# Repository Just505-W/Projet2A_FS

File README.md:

# Projet2A\_FS

Bienvenu sur le dépot GitHub d'un des groupes de Projet de deuxième année de l'ENSEA.  
Participants du projet :  
WOELFFEL Justine           NOICI Amélie  
IGIER Charles                  FORBICE Mattéo  
GERVAIS Joseph

Professeur encadrant : M.Seigneurbieux

Ce projet a pour objectif de réaliser des composants utiles au bon fonctionnement d'une monoplace dans le cadre du concours **FORMULA STUDENT**. Nous avions déjà réalisé plusieurs cartes l'année passée - il s'agit d'un odomètre, BMS, datalogger, carte de puissance et carte de contrôle. Nous allons reprendre ces carte avec pour objectif que concevoir une première version de ce que l'on voudra à terme présenter au concours.

## Objectifs

|MÉCANIQUE|ÉLECTRIQUE DE PUISSANCE|ÉLECTRONIQUE BASSE TENSION|LOGICIEL|SÉCURITÉ|GESTION DE PROJET|
|:-:|:-:|:-:|:-:|:-:|:-:|
|Châssis|Batterie|Alimentation 12 V|Firmware|Arrêt d'urgence|Planning|
|Suspension|BMS|Microcontrôleur|Contrôle moteur|Isolation|Budget|
|Direction|Contacteurs|Capteurs|Acquisition|Coupure HV|Achats|
|Freinage|Précharge|Acquisition|Télémétrie|Interlocks|Fabrication|
|Roues/pneus|Fusibles|Température|Diagnostic|Protection contre les défauts|Documentation|
|Transmission|Distribution HV|Instrumentation|Interface éventuelle|Sécurité batterie|Tests|
|Supports moteur|Moteur|Courant|Gestion des erreurs|Sécurité mécanique|Validation|
|Ergonomie|Onduleur|Tension||Procédures de test|Règlement|
|Carrosserie éventuelle|Câblage|Vitesse||||
||Protections|Communication CAN||||
||Isolation|||||

:warning:

### Important : Soutenance le 15 décembre

#### Checklist : 

* Définir le rôle de chacun : 

  * Définir les tâches que chacun doit accomplir
* Faire le Gantt (ou du moins ce qu'il faut faire et quand il faut le faire)
* Documentation de ce qui à été fait :

  * Regrouper toutes les documentations
  * Objectifs ?
  * Conclusion lors du 15 décembre
  * Ce qu'on espère avant la prochaine soutenance

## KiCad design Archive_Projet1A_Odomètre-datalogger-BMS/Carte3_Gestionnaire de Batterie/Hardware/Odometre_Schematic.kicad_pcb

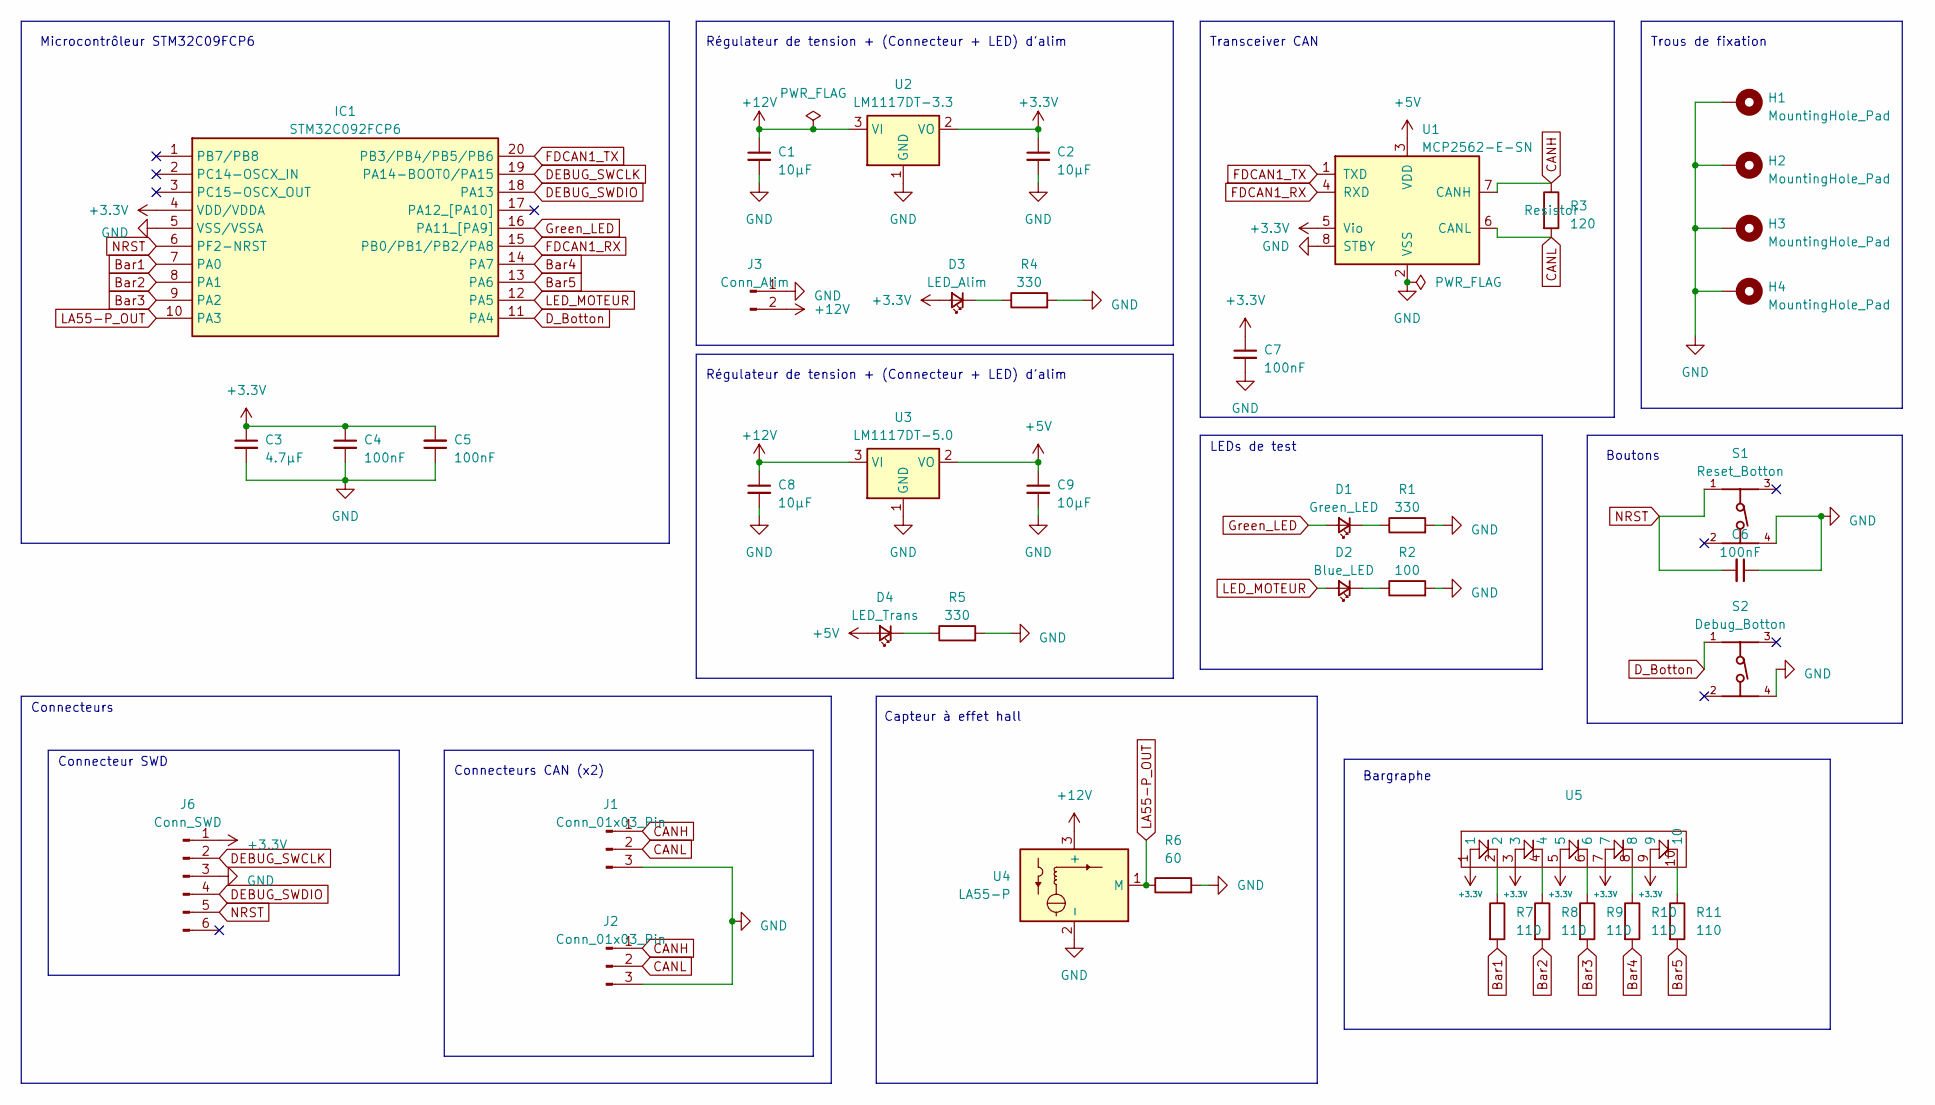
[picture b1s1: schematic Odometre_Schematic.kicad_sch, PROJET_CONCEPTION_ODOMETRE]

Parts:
C1, C2, C8, C9: 10µF; C_0805_2012Metric_Pad1.18x1.45mm_HandSolder
C3: 4.7µF; C_0805_2012Metric_Pad1.18x1.45mm_HandSolder
C4, C5, C6, C7: 100nF; C_0805_2012Metric_Pad1.18x1.45mm_HandSolder
D1: Green_LED; D_0603_1608Metric_Pad1.05x0.95mm_HandSolder
D2: Blue_LED; D_0603_1608Metric_Pad1.05x0.95mm_HandSolder
D3: LED_Alim; D_0603_1608Metric_Pad1.05x0.95mm_HandSolder
D4: LED_Trans; D_0603_1608Metric_Pad1.05x0.95mm_HandSolder
H1, H2, H3, H4: MountingHole_Pad; MountingHole_3.2mm_M3_DIN965_Pad
IC1: STM32C092FCP6; SOP65P640X120-20N; Manufacturer_Part_Number STM32C092FCP6
J1, J2: Conn_01x03_Pin; JST_PH_B3B-PH-K_1x03_P2.00mm_Vertical
J3: Conn_Alim; JST_PH_B2B-PH-K_1x02_P2.00mm_Vertical
J6: Conn_SWD; PinHeader_1x06_P2.54mm_Vertical
R1, R4, R5: 330; R_0603_1608Metric_Pad0.98x0.95mm_HandSolder
R2: 100; R_0603_1608Metric_Pad0.98x0.95mm_HandSolder
R3: 120; R_0603_1608Metric_Pad0.98x0.95mm_HandSolder
R6: 60; R_0603_1608Metric_Pad0.98x0.95mm_HandSolder
R7, R8, R9, R10, R11: 110; R_0603_1608Metric_Pad0.98x0.95mm_HandSolder
S1: Reset_Botton; 430182043816
S2: Debug_Botton; 430182043816
U1: MCP2562-E-SN; SOIC-8_3.9x4.9mm_P1.27mm
U2: LM1117DT-3.3; TO-252-3_TabPin2
U3: LM1117DT-5.0; TO-252-3_TabPin2
U4: LA55-P
U5: Projo

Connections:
+3.3V: C2.1, C3.1, C4.1, C5.2, C7.1, D3.2 (A), IC1.4 (VDD/VDDA), J6.1, U1.5 (Vio), U2.2 (VO), U5.1, U5.3, U5.5, U5.7, U5.9
+5V: C9.1, D4.2 (A), U1.3 (VDD), U3.2 (VO)
+12V: C1.1, C8.1, J3.2, U2.3 (VI), U3.3 (VI), U4.3 (+)
Bar1: IC1.7 (PA0), R7.2
Bar2: IC1.8 (PA1), R8.2
Bar3: IC1.9 (PA2), R9.2
Bar4: IC1.14 (PA7), R10.2
Bar5: IC1.13 (PA6), R11.2
CANH: J1.1, J2.1, R3.1, U1.7 (CANH)
CANL: J1.2, J2.2, R3.2, U1.6 (CANL)
DEBUG_SWCLK: IC1.19 (PA14-BOOT0/PA15), J6.2
DEBUG_SWDIO: IC1.18 (PA13), J6.4
D_Botton: IC1.11 (PA4), S2.1
FDCAN1_RX: IC1.15 (PB0/PB1/PB2/PA8), U1.4 (RXD)
FDCAN1_TX: IC1.20 (PB3/PB4/PB5/PB6), U1.1 (TXD)
GND: C1.2, C2.2, C3.2, C4.2, C5.1, C6.1, C7.2, C8.2, C9.2, H1.1, H2.1, H3.1, H4.1, IC1.5 (VSS/VSSA), J1.3, J2.3, J3.1, J6.3, R1.2, R2.2, R4.2, R5.2, R6.2, S1.4, S2.4, U1.2 (VSS), U1.8 (STBY), U2.1 (GND), U3.1 (GND), U4.2 (-)
Green_LED: D1.2 (A), IC1.16 (PA11_[PA9])
LA55-P_OUT: IC1.10 (PA3), R6.1, U4.1 (M)
LED_MOTEUR: D2.2 (A), IC1.12 (PA5)
NRST: C6.2, IC1.6 (PF2-NRST), J6.5, S1.1
unnamed: D1.1 (K), R1.1
unnamed: D2.1 (K), R2.1
unnamed: D3.1 (K), R4.1
unnamed: D4.1 (K), R5.1
unnamed: R7.1, U5.2
unnamed: R8.1, U5.4
unnamed: R9.1, U5.6
unnamed: R10.1, U5.8
unnamed: R11.1, U5.10

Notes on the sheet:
LEDs de test
Transceiver CAN
Connecteurs CAN (x2)
Régulateur de tension + (Connecteur + LED) d'alim
Connecteur SWD
Capteur à effet hall
Connecteurs
Boutons
Bargraphe
Microcontrôleur STM32C09FCP6
Trous de fixation

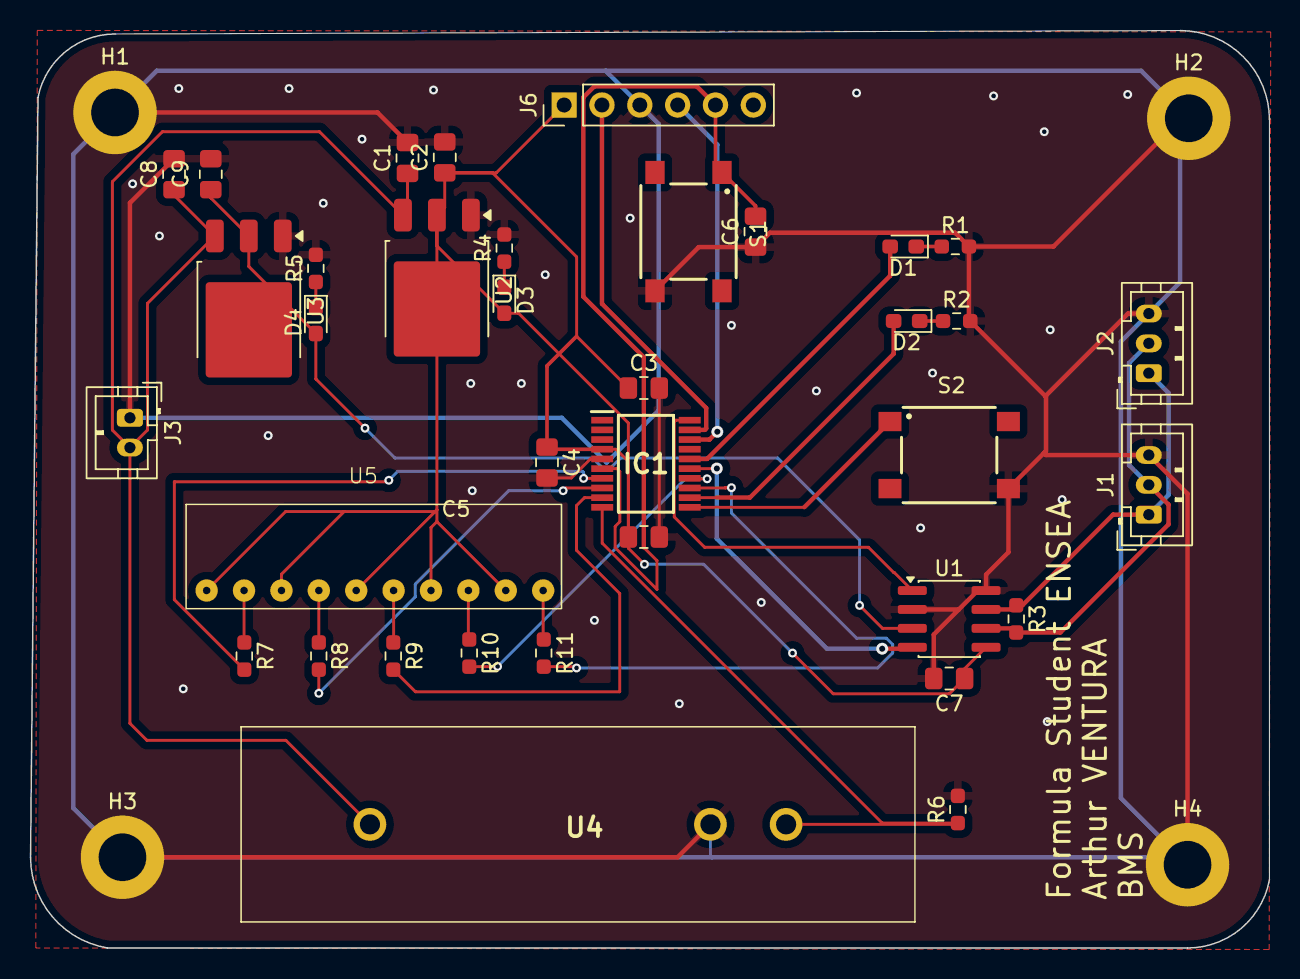
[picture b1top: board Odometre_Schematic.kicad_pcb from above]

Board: 2 copper layers, 83.2 x 61.6 mm, 40 parts (0 on the bottom side), 29 nets.

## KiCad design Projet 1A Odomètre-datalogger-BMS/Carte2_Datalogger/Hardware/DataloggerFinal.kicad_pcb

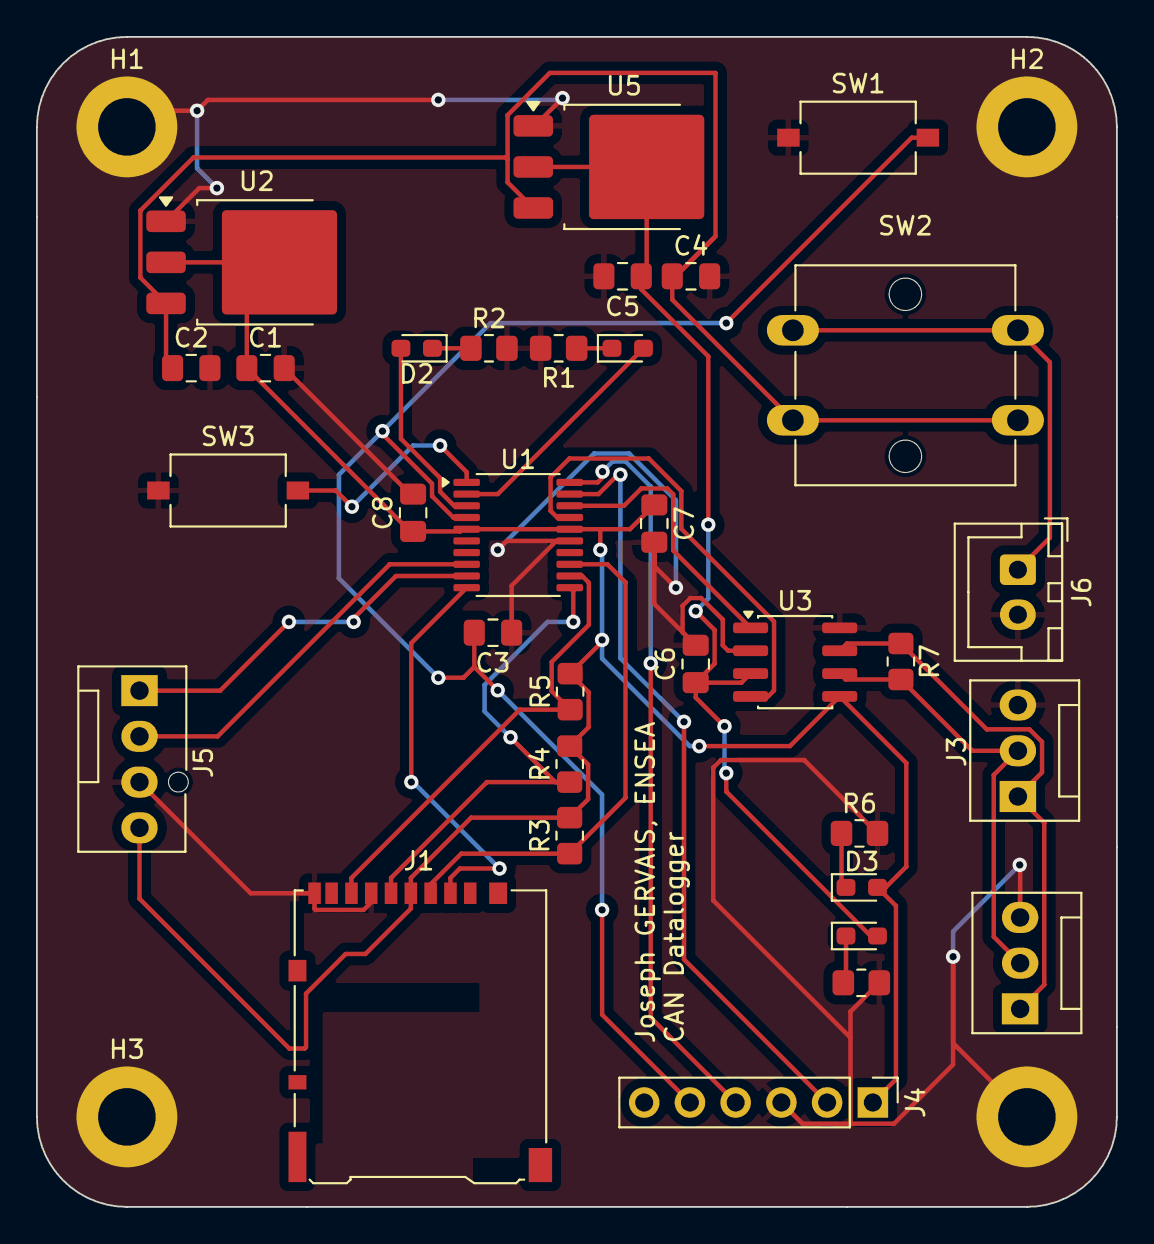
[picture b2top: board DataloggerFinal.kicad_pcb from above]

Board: 2 copper layers, 60.0 x 65.0 mm, 37 parts (0 on the bottom side), 25 nets.

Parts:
C1, C2, C4, C5: 10µF; C_0805_2012Metric_Pad1.18x1.45mm_HandSolder
C3: 1uF; C_0805_2012Metric_Pad1.18x1.45mm_HandSolder
C6, C7, C8: 100nF; C_0805_2012Metric_Pad1.18x1.45mm_HandSolder
D1, D2, D3, D4: LED; D_0603_1608Metric_Pad1.05x0.95mm_HandSolder
H1, H2, H3, H4: MountingHole_Pad; MountingHole_3.2mm_M3_DIN965_Pad
J1: Micro_SD_Card; microSD_HC_Hirose_DM3AT-SF-PEJM5
J2, J3: Conn_01x03_Pin; FanPinHeader_1x03_P2.54mm_Vertical
J4: Conn_01x06_Pin; PinHeader_1x06_P2.54mm_Vertical
J5: Conn_01x04_Pin; FanPinHeader_1x04_P2.54mm_Vertical
J6: Conn_01x02_Pin; JST_XH_B2B-XH-A_1x02_P2.50mm_Vertical
R1, R2, R6, R8: 1k; R_0805_2012Metric_Pad1.20x1.40mm_HandSolder
R3, R4, R5: 10k; R_0805_2012Metric_Pad1.20x1.40mm_HandSolder
R7: 120; R_0805_2012Metric_Pad1.20x1.40mm_HandSolder
SW1, SW3: SW_Push; SW_Tactile_SPST_NO_Straight_CK_PTS636Sx25SMTRLFS
SW2: SW_SPST; SW_SPST_Omron_B3F-40xx
U1: STM32F042F6Px; TSSOP-20_4.4x6.5mm_P0.65mm
U2: LM1117DT-3.3; TO-252-3_TabPin2
U3: MCP2562-E-SN; SOIC-8_3.9x4.9mm_P1.27mm
U5: LM1117DT-5.0; TO-252-3_TabPin2

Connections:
5V: C5.1, C6.1, D4.2 (A), U3.3 (VDD), U5.2 (VO)
+3.3V: C1.1, C7.1, C8.1, D3.2 (A), J1.4 (VDD), J4.1, J5.4, R3.2, R4.2, R5.2, U1.5 (VDDA), U1.16 (VDD), U2.2 (VO), U3.5 (Vio)
Alimentation: C2.1, C4.1, SW2.2 (B), U2.3 (VI), U5.3 (VI)
CAN_H: J2.1, J3.1, R7.1, U3.7 (CANH)
CAN_L: J2.2, J3.2, R7.2, U3.6 (CANL)
CAN_RX: U1.17 (PA9/PA11), U3.4 (RXD)
CAN_TX: U1.18 (PA10/PA12), U3.1 (TXD)
Debug_SWCLK: J4.2, U1.19 (PA13)
Debug_SWDIO: J4.4, U1.20 (PA14)
GND: C1.2, C2.2, C3.1, C4.2, C5.2, C6.2, C7.2, C8.2, H1.1, H2.1, H3.1, H4.1, J1.6 (VSS), J1.9 (SHIELD), J2.3, J3.3, J4.3, J5.3, J6.2, R1.2, R2.2, R6.2, R8.2, SW1.1, SW3.1, U1.15 (VSSA), U2.1 (GND), U3.2 (VSS), U3.8 (STBY), U5.1 (GND)
LED_Status_1: D1.2 (A), U1.2 (PF0)
LED_Status_2: D2.2 (A), U1.3 (PF1)
NRST: C3.2, J4.5, SW1.2, U1.4 (NRST)
unnamed: D1.1 (K), R1.1
unnamed: D2.1 (K), R2.1
unnamed: D3.1 (K), R6.1
unnamed: D4.1 (K), R8.1
unnamed: J6.1, SW2.1 (A)
SD_CS: J1.2 (DAT3/CD), U1.10 (PA4)
SD_SPI1_MISO: J1.7 (DAT0), R5.1, U1.12 (PA6)
SD_SPI1_MOSI: J1.3 (CMD), R3.1, U1.13 (PA7)
SD_SPI1_SCK: J1.5 (CLK), R4.1, U1.11 (PA5)
Test_PB: SW3.2, U1.1 (PB8)
USART2_RX: J5.1, U1.9 (PA3)
USART2_TX: J5.2, U1.8 (PA2)

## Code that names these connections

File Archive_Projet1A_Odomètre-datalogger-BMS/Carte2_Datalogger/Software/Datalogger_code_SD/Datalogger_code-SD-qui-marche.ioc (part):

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Mcu.Name=STM32F042F6Px
Mcu.Package=TSSOP20
Mcu.UserName=STM32F042F6Px
PA0.GPIOParameters=GPIO_Label
PA0.GPIO_Label=Test_PB
PA0.Signal=GPIO_Input
PA11.Mode=CAN_Activate
PA11.Signal=CAN_RX
PA12.Mode=CAN_Activate
PA12.Signal=CAN_TX
PA13.GPIOParameters=GPIO_Label
PA13.GPIO_Label=Debug_SWDIO
PA13.Mode=Serial_Wire
PA13.Signal=SYS_SWDIO
PA14.GPIOParameters=GPIO_Label
PA14.GPIO_Label=Debug_SWCLK
PA14.Mode=Serial_Wire
PA14.Signal=SYS_SWCLK
PA2.Mode=Asynchronous
PA2.Signal=USART2_TX
PA3.Mode=Asynchronous
PA3.Signal=USART2_RX
PA4.GPIOParameters=GPIO_Label
PA4.GPIO_Label=SD_CS
PA4.Mode=NSS_Signal_Hard_Output
PA4.Signal=SPI1_NSS
PA5.GPIOParameters=GPIO_Label
PA5.GPIO_Label=SD_SPI1_SCK
PA5.Mode=Full_Duplex_Master
PA5.Signal=SPI1_SCK
PA6.GPIOParameters=GPIO_Label
PA6.GPIO_Label=SD_SPI1_MISO
PA6.Mode=Full_Duplex_Master
PA6.Signal=SPI1_MISO
PA7.GPIOParameters=GPIO_Label
PA7.GPIO_Label=SD_SPI1_MOSI
PA7.Mode=Full_Duplex_Master
PA7.Signal=SPI1_MOSI
PF0-OSC_IN.GPIOParameters=GPIO_Label
PF0-OSC_IN.GPIO_Label=LED_Status_1
PF0-OSC_IN.Signal=GPIO_Output
PF1-OSC_OUT.GPIOParameters=GPIO_Label
PF1-OSC_OUT.GPIO_Label=LED_Status_2
PF1-OSC_OUT.Signal=GPIO_Output
board=custom

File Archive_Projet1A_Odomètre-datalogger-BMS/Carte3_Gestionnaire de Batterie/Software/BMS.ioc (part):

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Mcu.Name=STM32C092FCPx
Mcu.Package=TSSOP20
Mcu.UserName=STM32C092FCPx
PA0.GPIOParameters=GPIO_PuPd
PA0.GPIO_PuPd=GPIO_NOPULL
PA0.Signal=GPIO_Output
PA1.GPIOParameters=GPIO_PuPd
PA1.GPIO_PuPd=GPIO_NOPULL
PA1.Signal=GPIO_Output
PA11\ [PA9].Signal=GPIO_Output
PA13.Mode=Serial_Wire
PA13.Signal=DEBUG_SWDIO
PA14-BOOT0.Mode=Serial_Wire
PA14-BOOT0.Signal=DEBUG_SWCLK
PA14-BOOT0__PA15.StandardMode=true
PA2.GPIOParameters=GPIO_PuPd
PA2.GPIO_PuPd=GPIO_NOPULL
PA2.Signal=GPIO_Output
PA3.Signal=GPIO_Analog
PA4.GPIOParameters=GPIO_PuPd
PA4.GPIO_PuPd=GPIO_PULLUP
PA4.Signal=GPIO_Input
PA5.Signal=GPIO_Output
PA6.GPIOParameters=GPIO_PuPd
PA6.GPIO_PuPd=GPIO_NOPULL
PA6.Signal=GPIO_Output
PA7.GPIOParameters=GPIO_PuPd
PA7.GPIO_PuPd=GPIO_PULLDOWN
PA7.Signal=GPIO_Output
PB0.Mode=FDCAN_Activate
PB0.Signal=FDCAN1_RX
PB0__PB1__PB2__PA8.StandardMode=true
PB3__PB4__PB5__PB6.StandardMode=true
PB6.Mode=FDCAN_Activate
PB6.Signal=FDCAN1_TX
PB7.Mode=I2C
PB7.Signal=I2C1_SCL
PB7__PB8.StandardMode=true
PC14-OSCX_IN(PC14).Mode=I2C
PC14-OSCX_IN(PC14).Signal=I2C1_SDA
RCC.HSE_VALUE=8000000
RCC.SYSCLKFreq_VALUE=12000000
board=custom
